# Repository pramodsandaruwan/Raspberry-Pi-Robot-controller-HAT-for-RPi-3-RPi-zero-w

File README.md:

# Raspberry-pi-Robot-controller-HAT-for-RPi-3-RPi-zero-w
2 Layers PCB 30 x 65 mm FR-4, 1.6 mm, 1, HASL with lead, Green Solder Mask, White silkscreen

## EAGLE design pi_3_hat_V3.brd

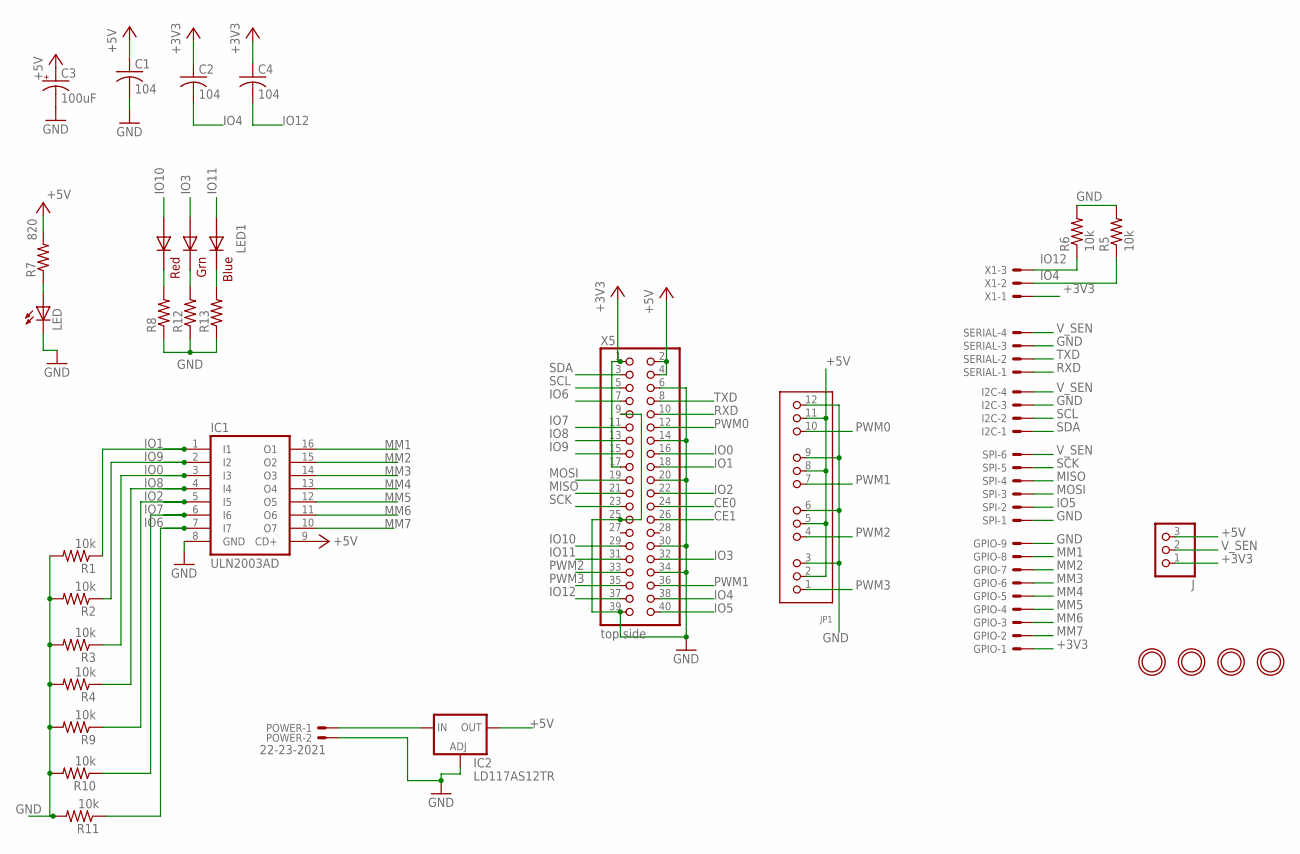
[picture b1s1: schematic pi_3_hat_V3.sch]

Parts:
C1, C2, C4: 104; C1206
C3: 100uF; E2,5-6
GPIO: 22-23-2091
I2C: 22-23-2041
IC1: ULN2003AD; SO16
IC2: LD117AS12TR; SOT223
J: PINHD-1X3; 1X03
JP1: HEADER-3X04; 3X04
LED: LEDSMT1206; 1206
LED1: RGBLED5050
POWER: 22-23-2021
R1, R2, R3, R4, R5, R6, R9, R10, R11: 10k; R1206
R7: 820; R1206
R8, R12, R13: R-US_R1206; R1206
SERIAL: 22-23-2041
SPI: 22-23-2061
U$4, U$5, U$6, U$7: MOUNTINGHOLE2.5; MOUNTINGHOLE_2.5_PLATED
X1: 22-23-2031
X5: top side; 2X20

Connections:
+3V3: C2.1, C4.1, GPIO.1, J.1, X1.1, X5.1, X5.17
+5V: C1.1, C3.+, IC1.9 (CD+), IC2.4 (OUT), J.3, JP1.2, JP1.5, JP1.8, JP1.11, R7.2, X5.2, X5.4
CE0: X5.24
CE1: X5.26
GND: C1.2, C3.-, GPIO.9, I2C.3, IC1.8 (GND), IC2.1 (ADJ), JP1.3, JP1.6, JP1.9, JP1.12, LED.C, POWER.2, R1.2, R2.2, R3.2, R4.2, R5.2, R6.2, R8.1, R9.2, R10.2, R11.2, R12.1, R13.1, SERIAL.3, SPI.1, X5.6, X5.9, X5.14, X5.20, X5.25, X5.30, X5.34, X5.39
IO0: IC1.3 (I3), R3.1, X5.16
IO1: IC1.1 (I1), R1.1, X5.18
IO2: IC1.5 (I5), R9.1, X5.22
IO3: LED1.1 (GREEN_A), X5.32
IO4: C2.2, R5.1, X1.2, X5.38
IO5: SPI.2, X5.40
IO6: IC1.7 (I7), R11.1, X5.7
IO7: IC1.6 (I6), R10.1, X5.11
IO8: IC1.4 (I4), R4.1, X5.13
IO9: IC1.2 (I2), R2.1, X5.15
IO10: LED1.2 (RED_A), X5.29
IO11: LED1.3 (BLUE_A), X5.31
IO12: C4.2, R6.1, X1.3, X5.37
MISO: SPI.4, X5.21
MM1: GPIO.8, IC1.16 (O1)
MM2: GPIO.7, IC1.15 (O2)
MM3: GPIO.6, IC1.14 (O3)
MM4: GPIO.5, IC1.13 (O4)
MM5: GPIO.4, IC1.12 (O5)
MM6: GPIO.3, IC1.11 (O6)
MM7: GPIO.2, IC1.10 (O7)
MOSI: SPI.3, X5.19
unnamed: LED.A, R7.1
unnamed: LED1.5 (RED_C), R8.2
unnamed: IC2.3 (IN), POWER.1
unnamed: LED1.6 (GREEN_C), R12.2
unnamed: LED1.4 (BLUE_C), R13.2
PWM0: JP1.10, X5.12
PWM1: JP1.7, X5.36
PWM2: JP1.4, X5.33
PWM3: JP1.1, X5.35
RXD: SERIAL.1, X5.10
SCK: SPI.5, X5.23
SCL: I2C.2, X5.5
SDA: I2C.1, X5.3
TXD: SERIAL.2, X5.8
V_SEN: I2C.4, J.2, SERIAL.4, SPI.6

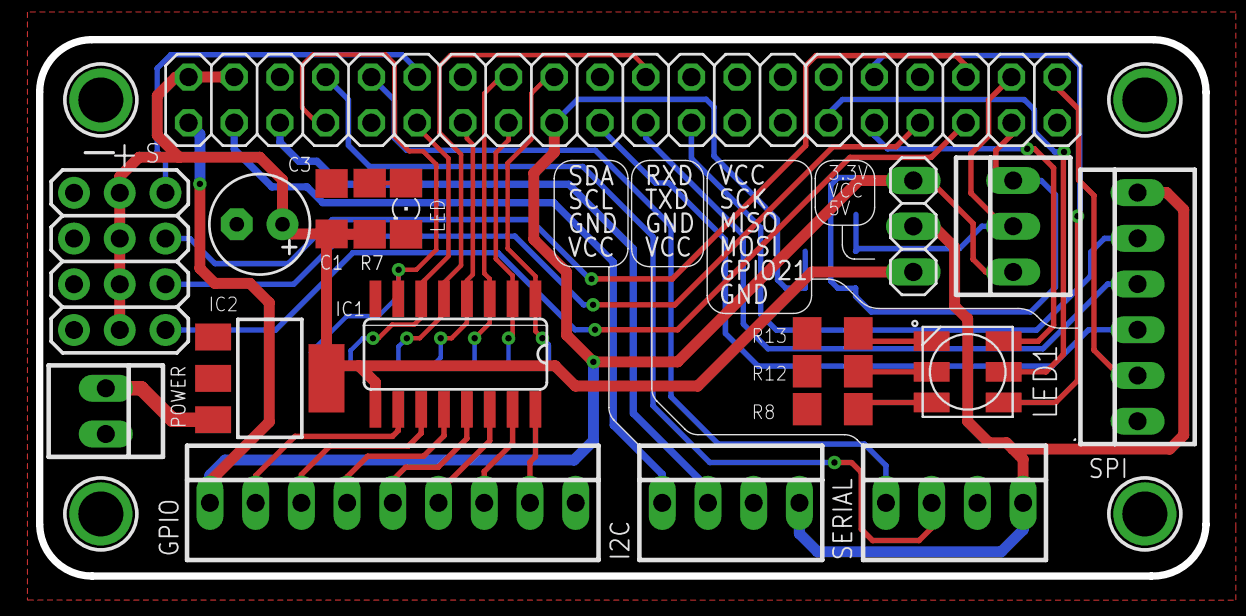
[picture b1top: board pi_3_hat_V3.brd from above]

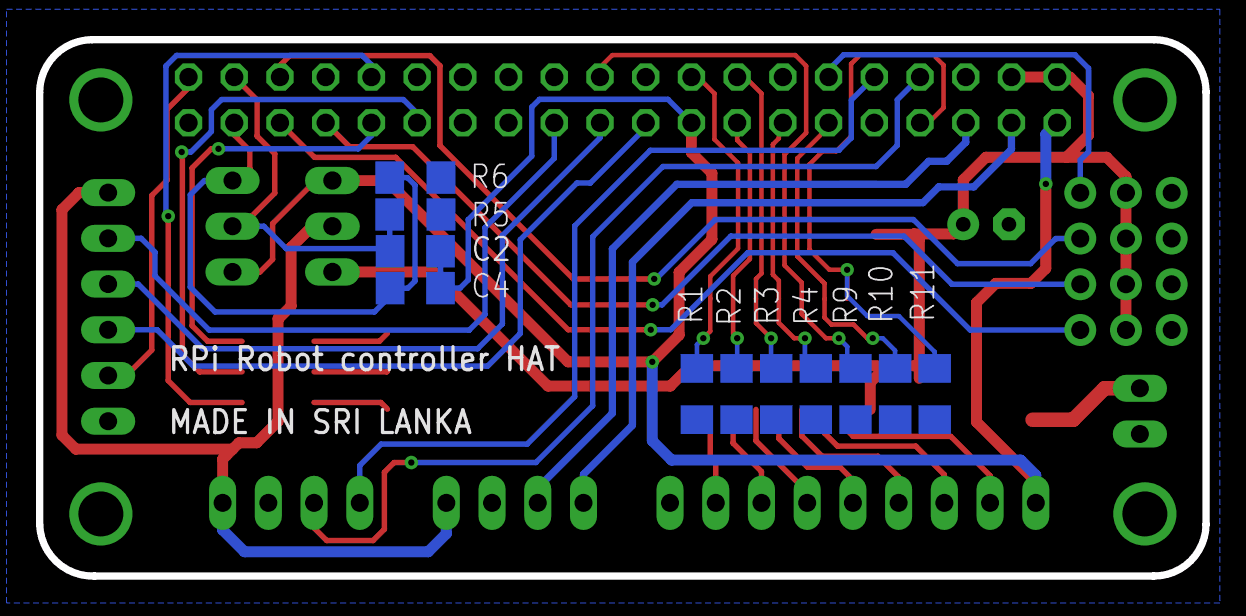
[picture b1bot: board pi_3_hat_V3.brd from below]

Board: 2 copper layers, 64.8 x 29.8 mm, 34 parts (11 on the bottom side), 40 nets.
